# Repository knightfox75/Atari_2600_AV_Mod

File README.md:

# Atari_2600_AV_Mod
 Adds AV output to an Atari 2600 (PAL) video console

https://nightfoxandco.com/?page_id=1341

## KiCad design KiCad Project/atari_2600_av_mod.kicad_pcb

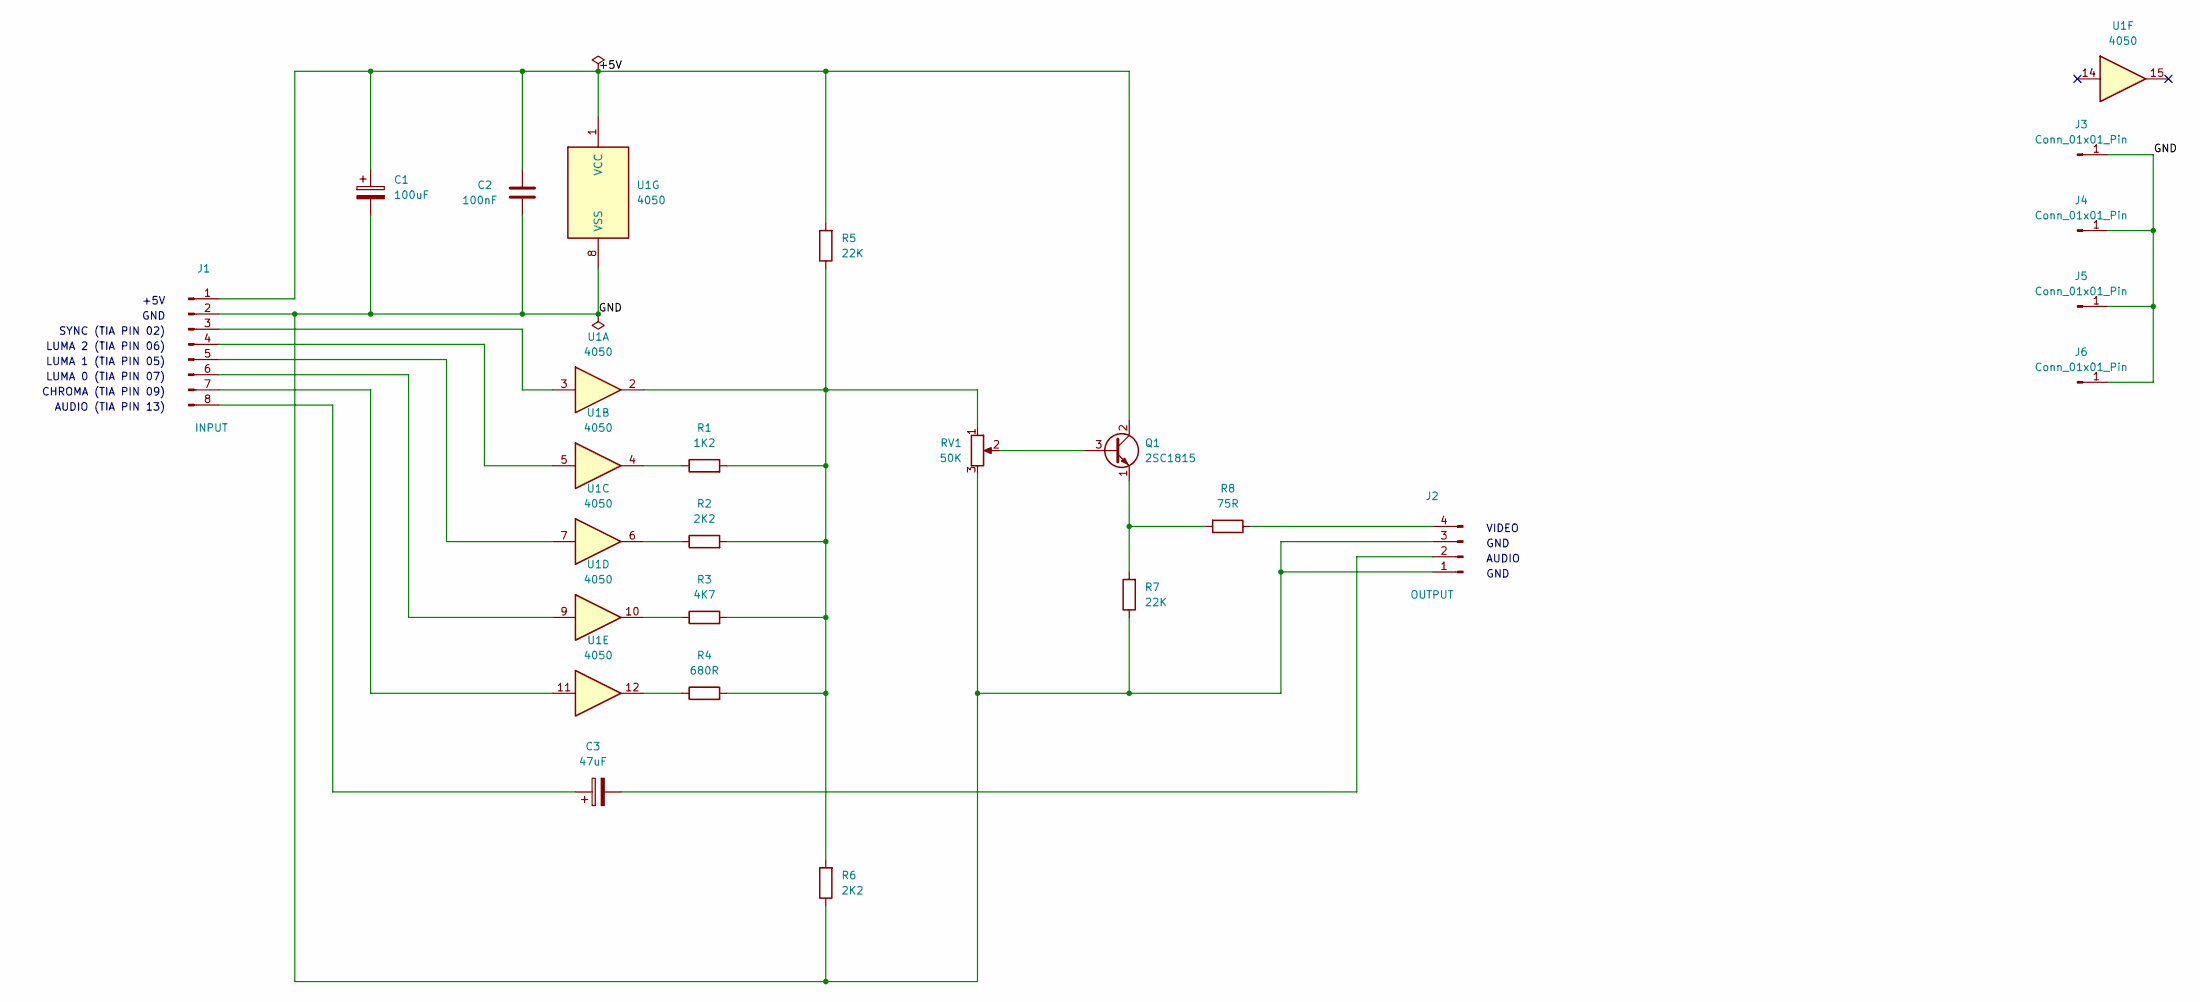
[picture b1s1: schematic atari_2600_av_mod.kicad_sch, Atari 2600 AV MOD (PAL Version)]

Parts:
C1: 100uF; CP_Radial_D6.3mm_P2.50mm
C2: 100nF; C_Disc_D6.0mm_W2.5mm_P5.00mm
C3: 47uF; CP_Radial_D6.3mm_P2.50mm
J1: INPUT; PinHeader_1x08_P2.54mm_Vertical
J2: OUTPUT; PinHeader_1x04_P2.54mm_Vertical
J3, J4, J5, J6: Conn_01x01_Pin; PinHeader_1x01_P2.54mm_Vertical
Q1: 2SC1815; TO-92_HandSolder
R1: 1K2; R_Axial_DIN0207_L6.3mm_D2.5mm_P2.54mm_Vertical
R2, R6: 2K2; R_Axial_DIN0207_L6.3mm_D2.5mm_P2.54mm_Vertical
R3: 4K7; R_Axial_DIN0207_L6.3mm_D2.5mm_P2.54mm_Vertical
R4: 680R; R_Axial_DIN0207_L6.3mm_D2.5mm_P2.54mm_Vertical
R5, R7: 22K; R_Axial_DIN0207_L6.3mm_D2.5mm_P2.54mm_Vertical
R8: 75R; R_Axial_DIN0207_L6.3mm_D2.5mm_P2.54mm_Vertical
RV1: 50K; Potentiometer_Bourns_3266Y_Vertical
U1: 4050; DIP-16_W7.62mm_Socket

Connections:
/+5V: C1.1, C2.1, J1.1, Q1.2 (C), R5.2, U1.1 (VCC)
/GND: C1.2, C2.2, J1.2, J2.1, J2.3, J3.1, J4.1, J5.1, J6.1, R6.1, R7.1, RV1.3, U1.8 (VSS)
unnamed: J1.3, U1.3
unnamed: J1.4, U1.5
unnamed: J1.5, U1.7
unnamed: J1.6, U1.9
unnamed: J1.7, U1.11
unnamed: C3.1, J1.8
unnamed: C3.2, J2.2
unnamed: J2.4, R8.1
unnamed: Q1.3 (B), RV1.2
unnamed: Q1.1 (E), R7.2, R8.2
unnamed: R1.1, U1.4
unnamed: R1.2, R2.2, R3.2, R4.2, R5.1, R6.2, RV1.1, U1.2
unnamed: R2.1, U1.6
unnamed: R3.1, U1.10
unnamed: R4.1, U1.12

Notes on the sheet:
LUMA 0 (TIA PIN 07)
+5V
SYNC (TIA PIN 02)
LUMA 1 (TIA PIN 05)
GND
AUDIO (TIA PIN 13)
CHROMA (TIA PIN 09)
AUDIO
VIDEO
LUMA 2 (TIA PIN 06)

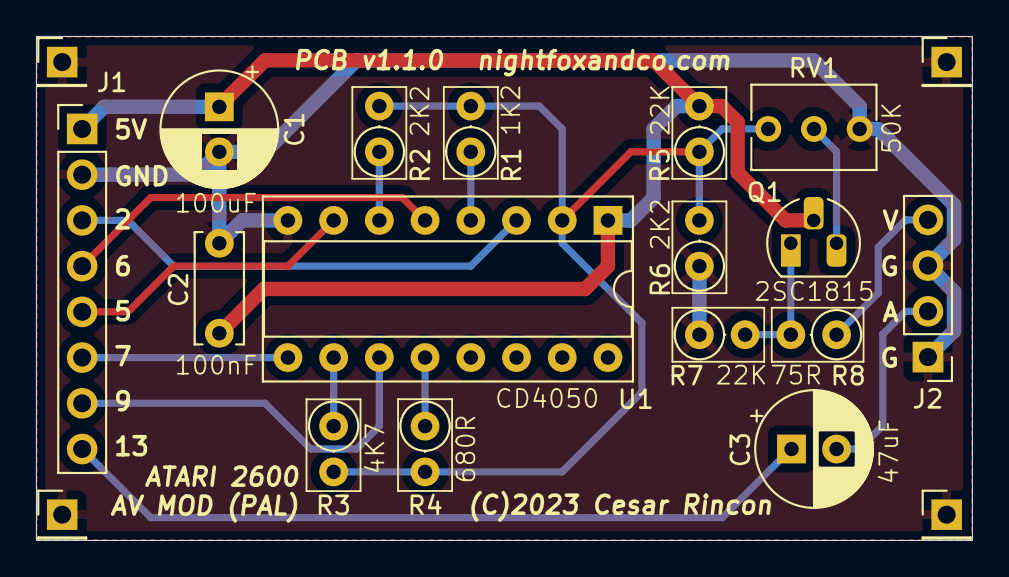
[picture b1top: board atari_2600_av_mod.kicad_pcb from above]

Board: 2 copper layers, 52.0 x 28.0 mm, 20 parts (0 on the bottom side), 17 nets.

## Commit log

2023-08-20 v1.0.0
    Initial release.
2023-09-06 v1.1.0
    - Updated 2SC1815 footprint.

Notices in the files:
KiCad Project/atari_2600_av_mod.kicad_pcb:
(C)2023 Cesar Rincon
